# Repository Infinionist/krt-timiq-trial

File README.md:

# krt-timiq-trial

A placement trial of KiCadRoutingTools (KRT) v0.23.7 (commit db056e03) on the CERN TimIQ RF board.
@edgehero suggested the board. The work was done by a designer (Infinionist) driving Claude Code.
The board has 465 parts, 8 layers, 6 shield cans (J7-J12) and sits in a Hammond 1590Q lid.

This is raw working material, not a polished report. Point your own model at it.
Start with `notes/timiq.md`, then `runs/v6/REPORT.md`.

v6 is the run done the skill's way: the model reads the schematic, gets the physical facts and the
designer's intent, and runs the skill's rounds (3, 3 and 12 seeds). The earlier runs were our own
scripted variants and show where our setup went wrong.

Board source (CERN open hardware): https://gitlab.com/ohwr/project/timiq/timiq-hw

## Folders

- `notes/`: feedback notes for KRT (`timiq.md`: gaps, workarounds, where we leaned on the human board,
  results) and plans (`PLAN.md`, `PLAN-v2.md`).
- `scripts/`: small helper scripts shared by several runs.
- `runs/run1/`: first attempt, KRT's skill driven by Claude Opus with an empty design brief. 12 seeds, judge,
  final board with 557 blocking nets after routing.
- `runs/run2/`: second attempt. Plan v2 (see `notes/PLAN-v2.md`), prompt, inputs, and the can/hole/membership work files.
- `runs/v2/`: placer-only variant with our KRT patch. Scripts, intent, seeds, renders, human-board render.
- `runs/v3/`: loose anchor zones per can, courtyards synthesized, flippable faces. All 12 seeds illegal
  (our input bugs: a fixed LED in a hole keep-out, DAC bigger than its zone, overlapping zones). KRT flagged
  them only after 4 h of placing.
- `runs/v4/`: tight power strip and cans placed inside fixed zones, 6 seeds of 42 min. All 6 illegal
  (15-25 parts with no legal pose, mostly power). Our tiles were too tight.
- `runs/v5/`: holds `seeds-run1` (v5-1: all 282 can members inside their can, not DONE: 76 proximity misses,
  power entry split from regulators), `seeds-v4`, `seeds-run2` and `seeds` (v5b: power as loose groups, ICs locked
  on F; 3 seeds, all illegal, 7-9 parts with no legal pose). `cmp/` has the human-board comparison renders
  (human vs seed vs routed seed). `movie/` has the 3D placement movie.
- `runs/v6/`: the skill as written. `REPORT.md`, `final.kicad_pcb` (+ `.kicad_pro`, `final_intent.json`),
  `groups.json`, rounds `r1`/`r2`/`r3` (seed reports, logs, judge files, renders, best board per round),
  `best_*` renders, quick-route renders, `movie_r1..r3/placed_3d.mp4`, `ledger.jsonl`, start board, build scripts.
  Round 3: 6 of 12 seeds legal with 0 floorplan errors, the first legal placement of this board. Kept seed 7:
  buildable with BOX1 waivers, quick route 88 blocking (39 unrouted, 49 broken). Not DONE by the skill's table.
- `runs/retest/`: the #1457 retest (2026-10-30) at KRT main 8f0c7ef4 (v0.23.7), with the cans kept on the board as
  `cans[]` rows. `REPORT.md` (the run's own report), `compare.json` (vs v6), `final.kicad_pcb`, `intent.json`, `TimIQ_RF.design-brief.json` (the six `cans[]` rows),
  `seed3_with_cans.mp4` (the kept seed, with the can walls drawn in by `repro/add_cans.py`), `placed_3d.mp4`
  (make_movie as run), `repro/` (wall check, board_score repro). 12 of 12 seeds legal; kept seed 3.

## What was trimmed

- No vendor datasheets (copyright) and no KRT clone. Get KRT v0.23.7 from its own repo.
- Route working dirs (`s*_route/`) were dropped except `runs/v6/r3/s7_route`.
- Only the best few seed boards of each round or run are kept. The seed `.json` reports and logs are all there.
- `*.kicad_prl` files and movie frame directories (`placed_movie3d/`) were dropped; the `.mp4` files are kept.
- `runs/v6/preflight_r1.txt` was over 5 MB in the original; it keeps its first and last 300 lines only.
- The name of the designer was replaced with `Infinionist` and home paths with `~`.

## Honest limits

The runs say as much about our setup as about KRT. The cans were taken off the board as a workaround (KRT has no
way to place parts inside a fixed can). J7-J10 poses, can membership and hole clearances follow the human board.
See "Where we cheated or leaned on the human board" in `notes/timiq.md`.

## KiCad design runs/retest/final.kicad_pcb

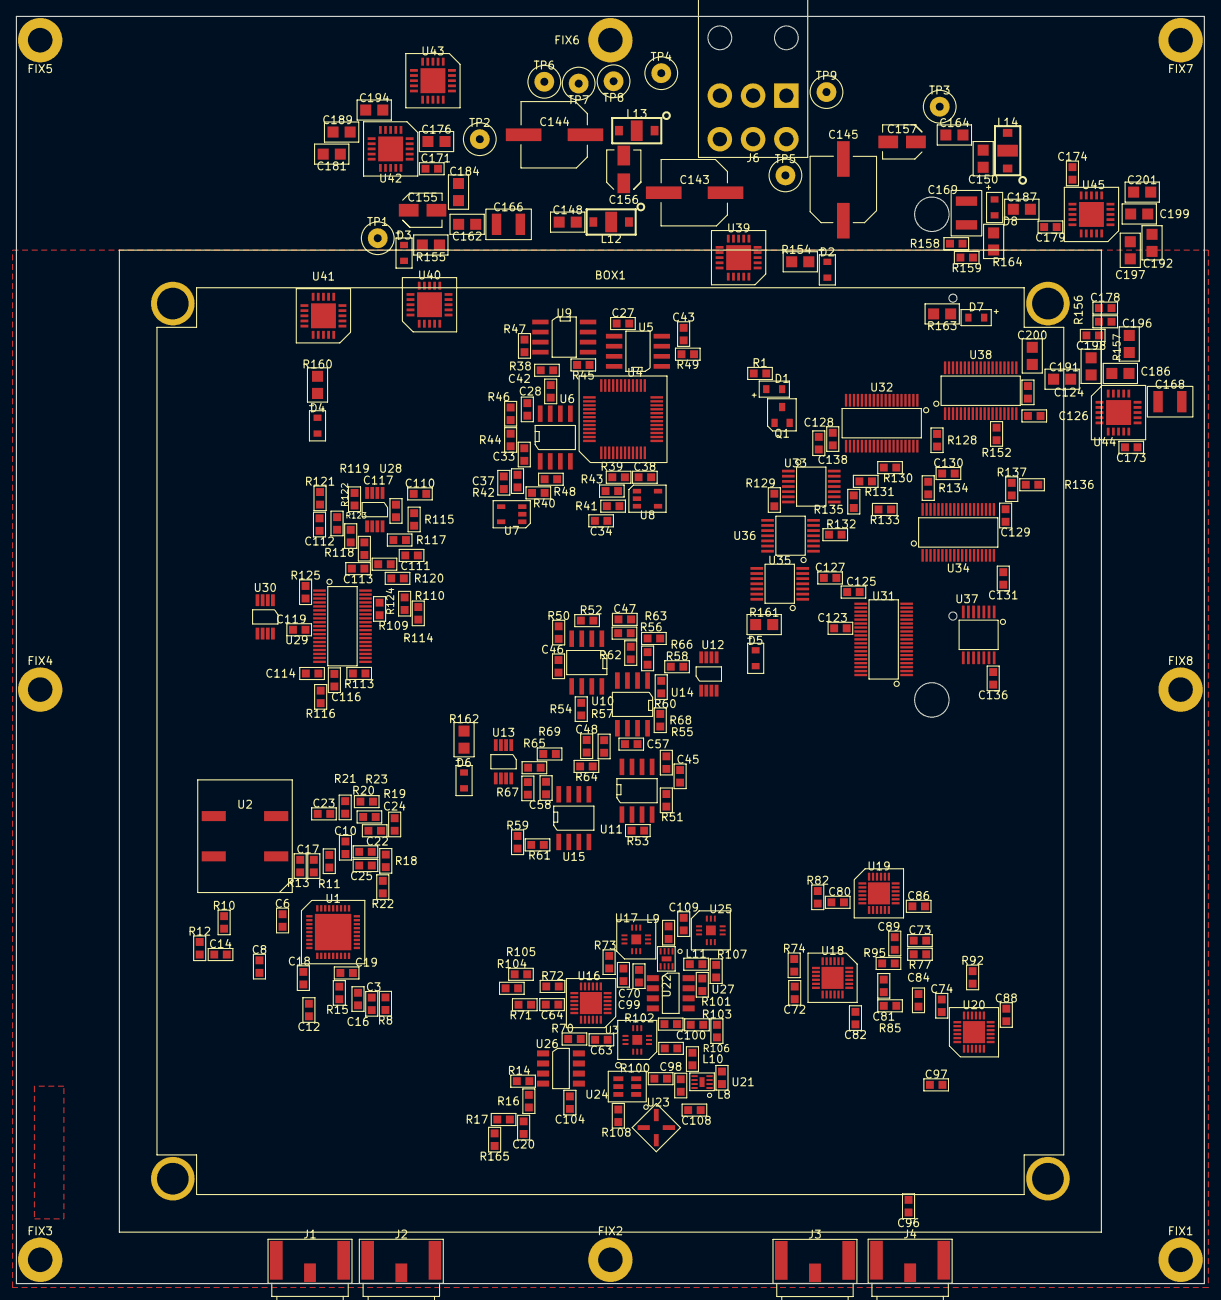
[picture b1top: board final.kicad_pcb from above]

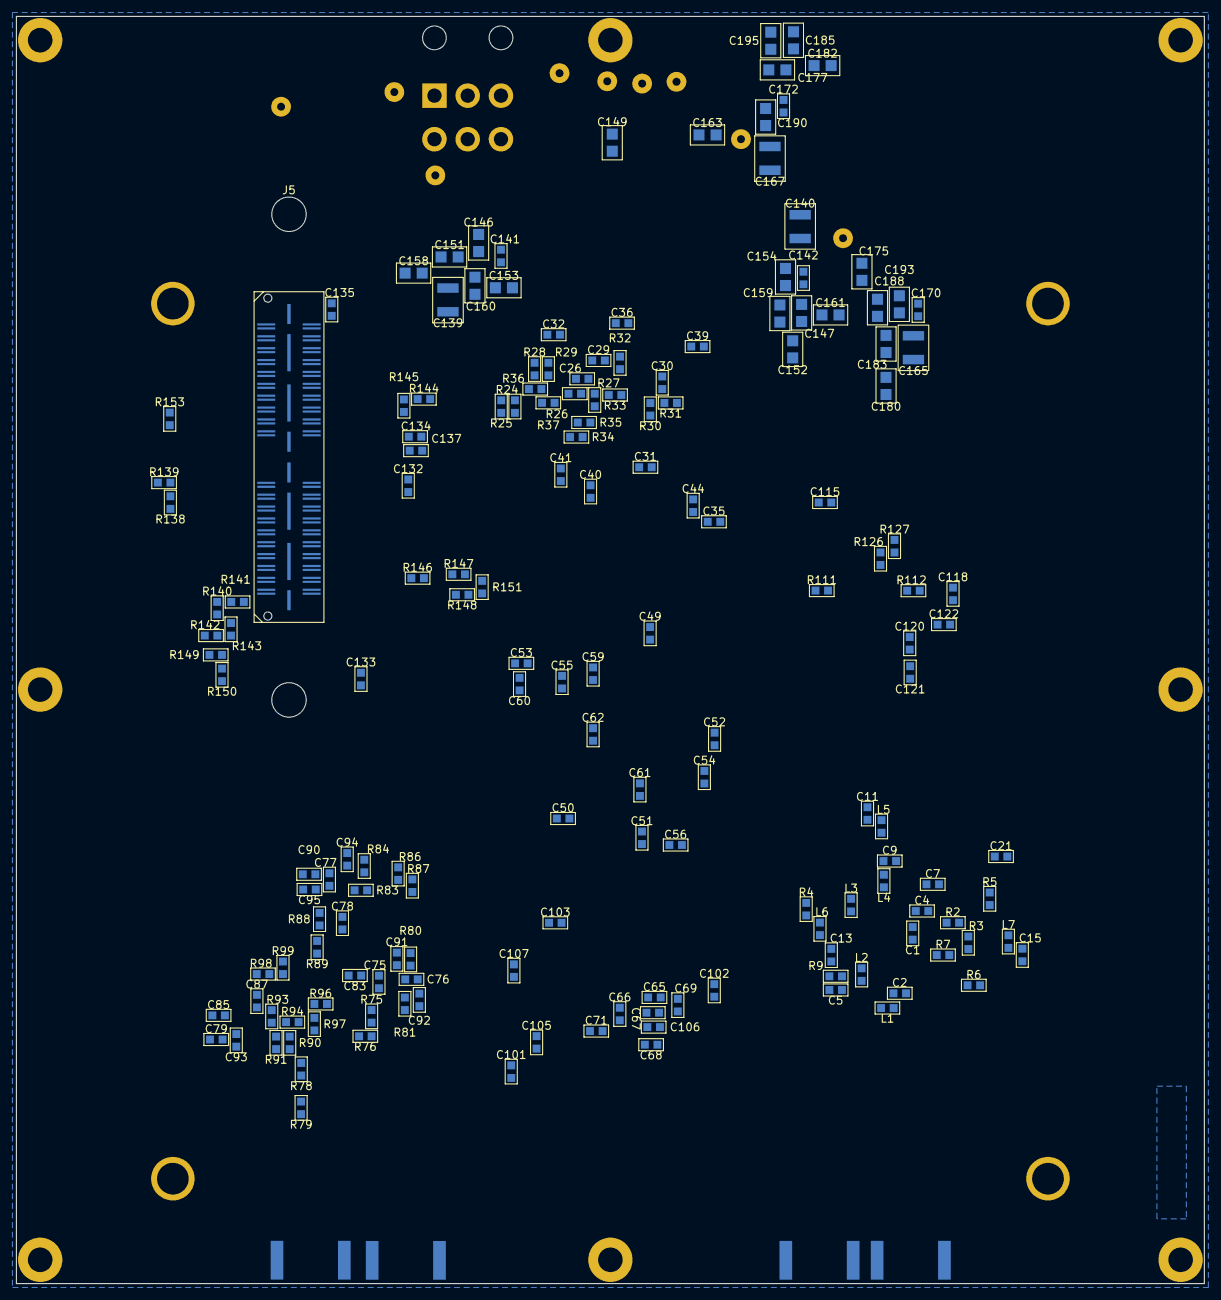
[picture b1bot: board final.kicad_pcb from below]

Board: 8 copper layers, 150.0 x 160.0 mm, 458 parts (167 on the bottom side), 298 nets, no tracks yet.

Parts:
BOX1: 1590Q; SOLEIL-1590Q
C1, C4, C6, C8, C65, C66, C74, C75, C82, C83, C90, C91: 10pF-50V-5p-Ceramic-0603; SOLEIL-0603
C2, C3, C7, C9, C11, C12, C13, C15, C24, C51, C52, C55, C56, C57, C58, C119: 100nF-50V-10p-Ceramic-0603; SOLEIL-0603
C5, C10, C33, C34, C37, C38, C120, C141, C142, C170, C171, C172, C173, C174: 1uF-25V-10p-Ceramic-0603; SOLEIL-0603
C14, C69, C71, C78, C79, C86, C87, C94, C95, C100, C102, C104, C106: 4.7uF-6.3V-10p-Ceramic-0603; SOLEIL-0603
C16, C20, C23, C27, C28, C42, C43, C47, C48, C63, C64, C70, C72, C73, C80, C81, C88, C89, C96, C97, C98, C99, C101, C103, C105, C107, C108, C109: 100pF-50V-5p-Ceramic-0603; SOLEIL-0603
C17, C19, C22, C25: 22nF-50V-10p-Ceramic-0603; SOLEIL-0603
C18: 2.2nF-50V-5p-Ceramic-0603; SOLEIL-0603
C21, C67, C68, C76, C77, C84, C85, C92, C93: 1nF-50V-5p-Ceramic-0603; SOLEIL-0603
C26, C29, C30, C31, C32, C35, C36, C39, C40, C41, C44, C45, C46, C49, C50, C59, C60, C61, C62, C114, C115, C116, C117, C118, C123, C124, C125, C126, C127, C128, C129, C130, C131, C132, C133, C134, C135, C136, C137, C138, C178, C179: 10nF-25V-5p-Ceramic-0603; SOLEIL-0603
C53, C54, C122: 10uF-6.3V-10p-Ceramic-0603; SOLEIL-0603
C110, C111: 330pF-50V-5p-Ceramic-0603; SOLEIL-0603
C112, C113: 1.5nF-50V-5p-Ceramic-0603; SOLEIL-0603
C121: 22uF-10V-20p-Ceramic-0603; SOLEIL-0603
C139, C140, C165, C166, C167, C168, C169: 10uF-25V-10p-Ceramic-1210; SOLEIL-1210
C143, C144, C145: 100uF-16V-20p-Al-TypeE; SOLEIL-TYPEE
C146, C147, C151, C152, C153, C154, C158, C159, C160, C161, C175, C176, C177, C180, C181, C182, C183, C184, C185, C186, C187, C188, C189, C190, C191, C192, C193, C194, C195, C196, C197, C198, C199, C200, C201: 10uF-16V-10p-Ceramic-0805; SOLEIL-0805
C148, C149, C150, C162, C163, C164: 100nF-50V-10p-Ceramic-0805; SOLEIL-0805
C155, C156, C157: 10uF-16V-20p-Al-TypeB; SOLEIL-TYPEB
D1, D2, D3, D4, D5, D6, D7, D8: LG_M67K-G1J2-24; SOLEIL-M67K
FIX1, FIX2, FIX3, FIX4, FIX5, FIX6, FIX7, FIX8: D_3mm1; SOLEIL-D_3mm1
J1, J2, J3, J4: 132430; SOLEIL-SMA-132430
J5: QSH-040-01-F-D-DP-A; SOLEIL-QSH-040-01-F-D-DP-A
J6: 39-30-1061; SOLEIL-39-30-1061
L1, L2, L3, L4, L5, L6, L7: BLM18AG102SN1D; SOLEIL-0603
L8, L9: 10nH-1.4A-2p-4.3GHz-0603; SOLEIL-0603
L10, L11: 8.2nH-700mA-2p-4.2GHz-0603; SOLEIL-0603
L12, L13, L14: NFM41PC155B1H3L; SOLEIL-NFM41P
Q1: BSH103; SOLEIL-SOT23-3
R1, R2, R5, R7, R38, R39, R44, R45, R48, R49, R50, R51, R52, R53, R110, R112, R114, R125, R127, R129, R130, R131: 1K-0.166W-0.1P-0603; SOLEIL-0603
R3, R13, R22, R25, R27, R29, R31, R33, R35, R37, R72, R76, R79, R81, R84, R87, R89, R91, R94, R97, R99, R133, R135, R137, R139, R141, R143, R145, R146, R147, R148, R150, R152, R153: 4K7-0.100W-0.1P-0603; SOLEIL-0603
R4, R6, R24, R26, R28, R30, R32, R34, R36, R40, R41, R42, R43, R75, R78, R80, R83, R86, R88, R90, R93, R96, R98, R109, R111, R113, R128, R132, R134, R136, R138, R140, R142, R144, R149, R151: 10k-0.125W-1P-0603; SOLEIL-0603
R8, R10, R70, R71, R73, R74, R77, R82, R85, R92, R95, R100, R101, R108, R165: 50R5-0.150W-0.1P-0603; SOLEIL-0603
R9, R12: 4R7-0.100W-1P-0603; SOLEIL-0603
R11, R46, R47: 10R-0.125W-1P-0603; SOLEIL-0603
R14, R17, R19, R23: 330R-0.250W-1P-0603; SOLEIL-0603
R15, R54, R55, R106, R107: 0R-0.100W-1P-0603; SOLEIL-0603
R16, R20, R21: 18R-0.250W-1P-0603; SOLEIL-0603
R18: 820R-0.250W-1P-0603; SOLEIL-0603
R56, R57: 4K02-0.166W-0.1P-0603; SOLEIL-0603
R58, R59, R62, R64: 976R-0.166W-0.1P-0603; SOLEIL-0603
R60, R61: 576R-0.166W-0.1P-0603; SOLEIL-0603
R63, R65: 62R-0.200W-1P-0603; SOLEIL-0603
R66, R67: 1K5-0.166W-0.1P-0603; SOLEIL-0603
R68, R69: 1K2-0.100W-0.1P-0603; SOLEIL-0603
R102, R104: 5K11-0.166W-0.1P-0603; SOLEIL-0603
R103, R105: 49R9-0.166W-0.1P-0603; SOLEIL-0603
R115, R116: 7K5-0.166W-0.1P-0603; SOLEIL-0603
R117, R118: 14K-0.166W-0.1P-0603; SOLEIL-0603
R119, R120, R126: 10K-0.166W-0.1P-0603; SOLEIL-0603
R121, R122: 10M-0.100W-1P-0603; SOLEIL-0603
R123, R124: 88K7-0.166W-0.1P-0603; SOLEIL-0603
R154, R155, R163: 1K5-0.125W-1P-0805; SOLEIL-0805
R156: 332K-0.100W-1P-0603; SOLEIL-0603
R157: 102K-0.100W-1P-0603; SOLEIL-0603
R158: 1M24-0.100W-1P-0603; SOLEIL-0603
R159: 105K-0.100W-1P-0603; SOLEIL-0603
R160, R161: 1K-0.125W-1P-0805; SOLEIL-0805
R162, R164: 4K7-0.125W-1P-0805; SOLEIL-0805
TP1, TP2, TP3, TP4, TP5, TP6, TP7, TP8, TP9: TEST-22; SOLEIL-TEST-22
U1: LMX2541SQ2690E; SOLEIL-WQFN36
U2: CVHD-950M-108.3681; SOLEIL-SMD9x14
U3, U17, U25: GP2Y+; SOLEIL-DQ1225
U4: LTC2758ACLX; SOLEIL-LQFP48
U5, U6: LT1012ACS8; SOLEIL-SOIC8NB
U7, U8: LTC2054HVCS5; SOLEIL-SOT23-5
U9: LTC6241HVCS8; SOLEIL-SOIC8NB
U10, U11: LT1360CS8; SOLEIL-SOIC8NB
U12, U13: LTC6655BHMS8-1.25; SOLEIL-MSOP8
U14, U15: LT6600CS8-2.5; SOLEIL-SOIC8NB
U16: HMC1097LP4E; SOLEIL-WQFN24
U18, U19, U20: HMC705LP4E; SOLEIL-WQFN24
U21, U22: PMA2-43LN+; SOLEIL-MC1631
U23: GAT-5+; SOLEIL-FG873
U24: QCN-34+; SOLEIL-FV1206-1
U26, U27: SIM-73L+; SOLEIL-HV1195
U28: OPA2209AIDGKR; SOLEIL-MSOP8
U29: ADS8694IDBT; SOLEIL-TSSOP38-0.5
U30: LTC6655BHMS8-4.096; SOLEIL-MSOP8
U31, U32, U34: SN75LVDT388ADBT; SOLEIL-TSSOP38-0.5
U33, U35, U36, U37: SN74LV4T125PWR; SOLEIL-TSSOP14-0.65
U38: SN75LVDS389DBT; SOLEIL-TSSOP38-0.5
U39, U40, U41, U42, U43: TPS7A4700; SOLEIL-VQFN20
U44, U45: TPS7A3301; SOLEIL-VQFN20

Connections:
3V3_1: C1.1, C4.1, C6.1, C7.1, C8.1, C21.1, C175.1, C180.1, C183.1, C188.1, C193.1, L1.1, L2.1, L3.1, L4.1, L5.1, L6.1, L7.1, R4.1, R6.1, R160.1, U1.3, U1.7, U1.29, U1.31, U2.4, U41.1, U41.3, U41.20
3V3_2: C116.1, C123.1, C124.1, C125.1, C126.1, C127.1, C128.1, C129.1, C130.1, C131.1, C133.1, C134.1, C135.1, C137.1, C176.1, C181.1, C184.1, C189.1, C194.1, R109.1, R111.1, R113.1, R126.1, R128.1, R132.1, R134.1, R136.1, R138.1, R140.1, R142.1, R144.1, R149.1, R161.1, U29.34, U31.21, U31.29, U31.37, U32.21, U32.29, U32.37, U34.21, U34.29, U34.37, U35.14, U38.2, U38.10, U38.18, U42.1, U42.3, U42.20
5V_1: C74.1, C75.1, C76.1, C77.1, C78.1, C79.1, C82.1, C83.1, C84.1, C85.1, C86.1, C87.1, C90.1, C91.1, C92.1, C93.1, C94.1, C95.1, C136.1, C138.1, C146.1, C151.1, C153.1, C158.1, C160.1, R75.1, R78.1, R80.1, R83.1, R86.1, R88.1, R90.1, R93.1, R96.1, R98.1, R154.1, U18.9, U18.19, U19.9, U19.19, U20.9, U20.19, U36.14, U37.14, U39.1, U39.3, U39.20
5V_2: C26.1, C35.1, C36.1, C41.1, C51.1, C52.1, C59.1, C60.1, C65.1, C66.1, C67.1, C68.1, C69.1, C71.1, C104.1, C106.1, C114.1, C117.1, C118.1, C119.1, C132.1, C147.1, C152.1, C154.1, C159.1, C161.1, R1.1, R24.1, R26.1, R28.1, R30.1, R32.1, R34.1, R36.1, R102.1, R104.1, R106.1, R107.1, R151.1, R155.1, U4.5, U4.6, U4.16, U4.31, U4.32, U4.37, U4.38, U4.47, U4.48, U7.5, U8.5, U9.8, U12.1, U12.2, U13.1, U13.2, U14.3, U15.3, U16.18, U16.24, U28.8, U29.9, U29.30, U30.1, U30.2, U33.14, U40.1, U40.3, U40.20
7V5: C139.1, C140.1, C155.1, C162.1, C165.1, C166.1, L12.3, TP1.1, U39.13, U39.15, U39.16, U40.13, U40.15, U40.16, U41.13, U41.15, U41.16, U42.13, U42.15, U42.16
15V: C29.1, C30.1, C45.1, C46.1, C177.1, C182.1, C185.1, C190.1, C195.1, R162.1, U5.7, U6.7, U10.7, U11.7, U43.1, U43.3, U43.20
24V: C156.1, C163.1, C167.1, L13.3, TP2.1, U43.13, U43.15, U43.16
-5V: C39.1, C40.1, C44.1, C61.1, C62.1, C115.1, C178.1, C186.1, C191.1, C196.1, C198.1, C200.1, R156.1, R163.1, U7.2, U8.2, U9.4, U14.6, U15.6, U28.4, U44.1, U44.20
-15V: C31.1, C32.1, C49.1, C50.1, C179.1, C187.1, C192.1, C197.1, C199.1, C201.1, R158.1, R164.1, U5.4, U6.4, U10.4, U11.4, U45.1, U45.20
-24V: C157.2, C164.1, C168.1, C169.1, L14.3, TP3.1, U44.13, U44.15, U44.16, U45.13, U45.15, U45.16
/TOP/ADC//ADC_CS: R109.2, U29.38, U32.26
/TOP/ADC//ADC_RST: R111.2, U29.2, U32.27
/TOP/ADC/ADC_ALARM: R114.1, U29.35, U38.8
/TOP/ADC/ADC_MISO: R113.2, U29.36, U38.7
/TOP/ADC/ADC_MOSI: R112.1, U29.1, U32.23
/TOP/ADC/ADC_SCK: R110.1, U29.37, U32.24
/TOP/ADC/MIXERout0: R115.1, U26.2
/TOP/ADC/MIXERout1: R116.1, U27.2
/TOP/DAC Interface/DAC_I: C47.2, R54.2, R56.2, R62.1, U4.39, U4.40, U10.6
/TOP/DAC Interface/DAC_Q: C48.2, R55.2, R57.2, R64.1, U4.45, U4.46, U11.6
/TOP/DAC Interface/I_N: U14.5, U16.22
/TOP/DAC Interface/I_P: U14.4, U16.21
/TOP/DAC Interface/Q_N: U15.5, U16.9
/TOP/DAC Interface/Q_P: U15.4, U16.10
/TOP/DAC//DAC_CS: U4.11, U33.3
/TOP/DAC/DAC_MISO: R151.2, U4.14, U35.2
/TOP/DAC/DAC_MOSI: U4.12, U33.8
/TOP/DAC/DAC_SCK: U4.13, U33.6
/TOP/Frequency dividers/FD0_BYP: U18.24, U36.3
/TOP/Frequency dividers/FD0_DIV1: R80.2, R81.1, U18.7
/TOP/Frequency dividers/FD0_N0: U18.21, U36.8
/TOP/Frequency dividers/FD0_N1: U18.22, U36.6
/TOP/Frequency dividers/FD0_N2: R75.2, R76.1, U18.23
/TOP/Frequency dividers/FD0_S0: R78.2, R79.1, U18.20
/TOP/Frequency dividers/FD1_BYP: U19.24, U36.11
/TOP/Frequency dividers/FD1_DIV1: R88.2, R89.1, U19.7
/TOP/Frequency dividers/FD1_N0: U19.21, U37.6
/TOP/Frequency dividers/FD1_N1: U19.22, U37.3
/TOP/Frequency dividers/FD1_N2: R83.2, R84.1, U19.23
/TOP/Frequency dividers/FD1_S0: R86.2, R87.1, U19.20
/TOP/Frequency dividers/FD2_BYP: U20.24, U37.8
/TOP/Frequency dividers/FD2_DIV1: U20.7, U37.11
/TOP/Frequency dividers/FD2_N0: R96.2, R97.1, U20.21
/TOP/Frequency dividers/FD2_N1: R93.2, R94.1, U20.22
/TOP/Frequency dividers/FD2_N2: R90.2, R91.1, U20.23
/TOP/Frequency dividers/FD2_S0: R98.2, R99.1, U20.20
/TOP/Frequency dividers/IQout1: C72.1, R74.1, U17.9
/TOP/Frequency mixers/IQout0: C99.1, R101.1, U17.7
/TOP/Frequency mixers/PLLout0: C98.1, R100.1, U3.7
/TOP/IQ modulator/PLLout1: C63.1, R70.1, U3.9
/TOP/PLL/PLL_CE: R4.2, U1.11, U31.35
/TOP/PLL/PLL_CLK: R5.1, U1.33, U31.31
/TOP/PLL/PLL_DATA: R7.1, U1.32, U31.32
/TOP/PLL/PLL_ENout: R6.2, U1.24, U31.34
/TOP/PLL/PLL_IN: C3.1, U1.21
/TOP/PLL/PLL_LE: R2.1, U1.34, U31.27
/TOP/PLL/PLL_LOCKED: Q1.1, R3.1, U1.20, U38.5
/TOP/PLL/PLL_OUT: C16.1, U1.36
/TOP/digital interface//ADC_CS-N: J5.63, U32.14
/TOP/digital interface//ADC_CS-P: J5.61, U32.13
/TOP/digital interface//ADC_RST-N: J5.59, U32.12
/TOP/digital interface//ADC_RST-P: J5.57, U32.11
/TOP/digital interface//DAC_CS-N: J5.43, U32.2
/TOP/digital interface//DAC_CS-P: J5.41, U32.1
/TOP/digital interface/ADC_ALARM-N: J5.56, U38.31
/TOP/digital interface/ADC_ALARM-P: J5.54, U38.32
/TOP/digital interface/ADC_MISO-N: J5.52, U38.33
/TOP/digital interface/ADC_MISO-P: J5.50, U38.34
/TOP/digital interface/ADC_MOSI-N: J5.71, U32.19
/TOP/digital interface/ADC_MOSI-P: J5.69, U32.18
/TOP/digital interface/ADC_SCK-N: J5.67, U32.17
/TOP/digital interface/ADC_SCK-P: J5.65, U32.16
/TOP/digital interface/DAC_ENA: J5.73, U32.36
/TOP/digital interface/DAC_ENB: J5.75, U32.33
/TOP/digital interface/DAC_ENC: J5.77, U32.25
/TOP/digital interface/DAC_END: J5.79, U32.22
/TOP/digital interface/DAC_MISO-N: J5.48, U38.35
/TOP/digital interface/DAC_MISO-P: J5.46, U38.36
/TOP/digital interface/DAC_MOSI-N: J5.51, U32.7
/TOP/digital interface/DAC_MOSI-P: J5.49, U32.6
/TOP/digital interface/DAC_SCK-N: J5.47, U32.4
/TOP/digital interface/DAC_SCK-P: J5.45, U32.3
/TOP/digital interface/D_ENA: J5.58, U38.4
/TOP/digital interface/D_ENB: J5.60, U38.16
/TOP/digital interface/FD0_BYP-N: J5.4, U34.2
/TOP/digital interface/FD0_BYP-P: J5.2, U34.1
/TOP/digital interface/FD0_N0-N: J5.12, U34.7
/TOP/digital interface/FD0_N0-P: J5.10, U34.6
/TOP/digital interface/FD0_N1-N: J5.8, U34.4
/TOP/digital interface/FD0_N1-P: J5.6, U34.3
/TOP/digital interface/FD1_BYP-N: J5.16, U34.9
/TOP/digital interface/FD1_BYP-P: J5.14, U34.8
/TOP/digital interface/FD1_N0-N: J5.24, U34.14
/TOP/digital interface/FD1_N0-P: J5.22, U34.13
/TOP/digital interface/FD1_N1-N: J5.20, U34.12
/TOP/digital interface/FD1_N1-P: J5.18, U34.11
/TOP/digital interface/FD2_BYP-N: J5.28, U34.17
/TOP/digital interface/FD2_BYP-P: J5.26, U34.16
/TOP/digital interface/FD2_DIV1-N: J5.32, U34.19
/TOP/digital interface/FD2_DIV1-P: J5.30, U34.18
/TOP/digital interface/FD_ENA: J5.34, U34.36
/TOP/digital interface/FD_ENB: J5.36, U34.33
/TOP/digital interface/FD_ENC: J5.38, U34.25
/TOP/digital interface/FD_END: J5.40, U34.22
/TOP/digital interface/PLL_CE-N: J5.3, U31.2
/TOP/digital interface/PLL_CE-P: J5.1, U31.1
/TOP/digital interface/PLL_CLK-N: J5.15, U31.9
/TOP/digital interface/PLL_CLK-P: J5.13, U31.8
/TOP/digital interface/PLL_DATA-N: J5.11, U31.7
/TOP/digital interface/PLL_DATA-P: J5.9, U31.6
/TOP/digital interface/PLL_ENA: J5.33, U31.36
/TOP/digital interface/PLL_ENB: J5.35, U31.33
/TOP/digital interface/PLL_ENC: J5.37, U31.25
/TOP/digital interface/PLL_END: J5.39, U31.22
/TOP/digital interface/PLL_ENout-N: J5.7, U31.4
/TOP/digital interface/PLL_ENout-P: J5.5, U31.3
/TOP/digital interface/PLL_LE-N: J5.19, U31.12
/TOP/digital interface/PLL_LE-P: J5.17, U31.11
/TOP/digital interface/PLL_LOCKED-N: J5.44, U38.37
/TOP/digital interface/PLL_LOCKED-P: J5.42, U38.38
/TOP/digital interface/SPARE0-N: J5.23, U31.14
/TOP/digital interface/SPARE0-P: J5.21, U31.13
/TOP/digital interface/SPARE1-N: J5.27, U31.17
/TOP/digital interface/SPARE1-P: J5.25, U31.16
/TOP/digital interface/SPARE2-N: J5.31, U31.19
/TOP/digital interface/SPARE2-P: J5.29, U31.18
/TOP/digital interface/SPARE3-N: J5.55, U32.9
/TOP/digital interface/SPARE3-P: J5.53, U32.8
/TOP/digital interface/SPARE4-N: J5.64, U38.26
/TOP/digital interface/SPARE4-P: J5.62, U38.27
/TOP/digital interface/SPARE5-N: J5.68, U38.24
/TOP/digital interface/SPARE5-P: J5.66, U38.25
/TOP/digital interface/SPARE6-N: J5.72, U38.22
/TOP/digital interface/SPARE6-P: J5.70, U38.23
/TOP/digital interface/SPARE7-N: J5.76, U38.20
/TOP/digital interface/SPARE7-P: J5.74, U38.21
GND: BOX1.1, BOX1.3, BOX1.5, BOX1.7, C1.2, C2.2, C4.2, C5.2, C6.2, C8.2, C9.2, C10.2, C11.2, C12.2, C13.2, C14.2, C15.2, C17.2, C18.2, C19.2, C21.2, C26.2, C29.2, C30.2, C31.2, C32.2, C33.2, C34.2, C35.2, C36.2, C39.2, C40.2, C41.2, C44.2, C45.2, C46.2, C49.2, C50.2, C51.2, C52.2, C53.2, C54.2, C55.2, C56.2, C57.2, C58.2, C59.2, C60.2, C61.2, C62.2, C65.2, C66.2, C67.2, C68.2, C69.2, C71.2, C74.2, C75.2, C76.2, C77.2, C78.2, C79.2, C82.2, C83.2, C84.2, C85.2, C86.2, C87.2, C90.2, C91.2, C92.2, C93.2, C94.2, C95.2, C100.2, C101.2, C102.2, C103.2, C104.2, C105.2, C106.2, C107.2, C112.2, C113.2, C114.2, C115.2, C116.2, C117.2, C118.2, C119.2, C120.2, C121.2, C122.2, C123.2, C124.2, C125.2, C126.2, C127.2, C128.2, C129.2, C130.2, C131.2, C132.2, C133.2, C134.2, C135.2, C136.2, C137.2, C138.2, C139.2, C140.2, C141.2, C142.2, C143.2, C144.2, C145.1, C146.2, C147.2, C148.2, C149.2, C150.2, C151.2, C152.2, C153.2, C154.2, C155.2, C156.2, C157.1, C158.2, C159.2, C160.2, C161.2, C162.2, C163.2, C164.2, C165.2, C166.2, C167.2, C168.2, C169.2, C170.2, C171.2, C172.2, C173.2, C174.2, C175.2, C176.2, C177.2, C180.2, C181.2, C182.2, C183.2, C184.2, C185.2, C186.2, C187.2, C188.2, C189.2, C190.2, C191.2, C192.2, C193.2, C194.2, C195.2, C196.2, C197.2, C198.2, C199.2, C200.2, C201.2, D2.2, D3.2, D4.2, D5.2, D6.2, D7.1, D8.1, FIX1.1, FIX2.1, FIX3.1, FIX4.1, FIX5.1, FIX6.1, FIX7.1, FIX8.1, J1.2, J1.3, J1.4, J1.5, J2.2, J2.3, J2.4, J2.5, J3.2, J3.3, J3.4, J3.5, J4.2, J4.3, J4.4, J4.5, J5.81, J5.82, J5.83, J5.84, J5.85, J5.86, J5.87, J5.88, J6.2, J6.4, J6.6, L12.2, L13.2, L14.2, Q1.2, R2.2, R3.2, R5.2, R7.2, R8.2, R10.2, R14.2, R17.2, R18.2, R19.2, R23.2, R25.2, R27.2, R29.2, R31.2, R33.2, R35.2, R37.2, R46.2, R47.2, R50.2, R51.2, R52.2, R53.2, R60.2, R61.2, R63.2, R65.2, R68.2, R69.2, R70.2, R71.2, R72.2, R73.2, R74.2, R76.2, R77.2, R79.2, R81.2, R82.2, R84.2, R85.2, R87.2, R89.2, R91.2, R92.2, R94.2, R95.2, R97.2, R99.2, R100.2, R101.2, R108.2, R110.2, R112.2, R114.2, R119.2, R120.2, R121.2, R122.2, R125.2, R127.2, R129.2, R130.2, R131.2, R133.2, R135.2, R137.2, R139.2, R141.2, R143.2, R145.2, R146.1, R147.1, R148.1, R150.2, R152.1, R153.1, R157.2, R159.2, R165.2, TP4.1, TP5.1, TP6.1, TP7.1, TP8.1, TP9.1, U1.0, U1.1, U1.10, U1.27, U2.2, U3.0, U3.1, U3.3, U3.4, U3.5, U3.6, U3.8, U3.10, U3.11, U3.12, U4.4, U4.7, U4.8, U4.9, U4.10, U4.15, U4.17, U4.18, U4.27, U4.28, U4.29, U4.30, U4.33, U4.42, U4.43, U5.3, U6.3, U7.3, U8.3, U12.3, U12.4, U12.5, U12.8, U13.3, U13.4, U13.5, U13.8, U16.0, U16.2, U16.5, U16.8, U16.11, U16.12, U16.14, U16.17, U16.19, U16.20, U16.23, U17.0, U17.1, U17.3, U17.4, U17.5, U17.6, U17.8, U17.10, U17.11, U17.12, U18.0, U18.1, U18.2, U18.3, U18.4, U18.5, U18.6, U18.8, U18.10, U18.13, U18.14, U18.17, U18.18, U19.0, U19.1, U19.2, U19.3, U19.4, U19.5, U19.6, U19.8, U19.10, U19.13, U19.14, U19.17, U19.18, U20.0, U20.1, U20.2, U20.3, U20.4, U20.5, U20.6, U20.8, U20.10, U20.13, U20.14, U20.17, U20.18, U21.0, U21.3, U21.4, U21.5, U21.6, U21.8, U22.0, U22.3, U22.4, U22.5, U22.6, U22.8, U23.2, U23.4, U24.2, U24.5, U25.0, U25.1, U25.3, U25.4, U25.5, U25.6, U25.8, U25.10, U25.11, U25.12, U26.1, U26.3, U26.5, U26.6, U26.7, U27.1, U27.3, U27.5, U27.6, U27.7, U29.6, U29.8, U29.17, U29.19, U29.28, U29.29, U29.31, U29.32, U29.33, U30.3, U30.4, U30.5, U30.8, U31.5, U31.10, U31.15, U31.20, U31.28, U31.30, U31.38, U32.5, U32.10, U32.15, U32.20, U32.28, U32.30, U32.38, U33.1, U33.4, U33.7, U33.10, U33.13, U34.5, U34.10, U34.15, U34.20, U34.28, U34.30, U34.38, U35.1, U35.4, U35.7, U35.10, U35.13, U36.1, U36.4, U36.7, U36.10, U36.13, U37.1, U37.4, U37.7, U37.10, U37.13, U38.1, U38.3, U38.9, U38.11, U38.17, U38.19, U39.0, U39.6, U39.7, U39.10, U40.0, U40.6, U40.7, U40.10, U41.0, U41.7, U41.8, U41.11, U41.12, U42.0, U42.7, U42.8, U42.11, U42.12, U43.0, U43.4, U43.5, U43.7, U43.9, U44.0, U44.7, U45.0, U45.7
unnamed: C2.1, L1.2, U1.28
unnamed: C3.2, J1.1, R8.1
unnamed: C5.1, R9.1
unnamed: C7.2, U1.30
unnamed: C9.1, L4.2, U1.14
unnamed: C10.1, R11.2
unnamed: C11.1, L5.2, U1.18
unnamed: C12.1, U1.9
unnamed: C13.1, L6.2, U1.13
unnamed: C14.1, R12.2
unnamed: C15.1, L7.2, U1.19
unnamed: C16.2, R14.1, R16.1
unnamed: C17.1, R13.2, U2.1
unnamed: C18.1, R13.1, R15.2, U1.15
unnamed: C19.1, C22.1, C25.1, R15.1, U1.16
unnamed: C20.1, J2.1, R165.1
unnamed: C20.2, R16.2, R17.1, U3.2
unnamed: C22.2, C25.2, R18.1, R22.2
unnamed: C23.1, U2.3
unnamed: C23.2, R21.1
unnamed: C24.1, U1.12
unnamed: C24.2, R19.1, R20.1
unnamed: C27.1, U4.34, U5.2
unnamed: C27.2, U4.35, U4.36, U5.6
unnamed: C28.1, U4.3, U6.2
unnamed: C28.2, U4.1, U4.2, U6.6
unnamed: C33.1, R40.2, R42.1
unnamed: C34.1, R41.2, R43.1
unnamed: C37.1, R42.2, U7.4
unnamed: C37.2, R44.1, U7.1
unnamed: C38.1, R43.2, U8.4
unnamed: C38.2, R45.1, U8.1
unnamed: C42.1, R38.2, R40.1, R48.1, U9.2
unnamed: C42.2, R48.2, R50.1, R54.1, U9.1, U10.3
unnamed: C43.1, R39.2, R41.1, R49.1, U9.6
unnamed: C43.2, R49.2, R51.1, R55.1, U9.7, U11.3
unnamed: C47.1, R52.1, R56.1, U10.2
unnamed: C48.1, R53.1, R57.1, U11.2
unnamed: C53.1, R58.1, U12.6, U12.7
unnamed: C54.1, R59.1, U13.6, U13.7
unnamed: C55.1, R58.2, R60.1, U14.2
unnamed: C56.1, R59.2, R61.1, U15.2
unnamed: C57.1, U14.7
unnamed: C58.1, U15.7
unnamed: C63.2, U16.3
unnamed: C64.1, R71.1
unnamed: C64.2, U16.4
unnamed: C70.1, U16.16
unnamed: C70.2, R73.1, U17.2
unnamed: C72.2, U18.12
unnamed: C73.1, R77.1
unnamed: C73.2, U18.11
unnamed: C80.1, R82.1, U18.15
unnamed: C80.2, U19.12
unnamed: C81.1, R85.1, U18.16
unnamed: C81.2, U19.11
unnamed: C88.1, R92.1, U19.15
unnamed: C88.2, U20.12
unnamed: C89.1, R95.1, U19.16
unnamed: C89.2, U20.11
unnamed: C96.1, U20.15
unnamed: C96.2, J3.1
unnamed: C97.1, U20.16
unnamed: C97.2, J4.1
unnamed: C98.2, L8.2, U21.2
unnamed: C99.2, L9.2, U22.2
unnamed: C100.1, R102.2, R103.1
unnamed: C101.1, L8.1, R103.2, U21.1
unnamed: C102.1, R104.2, R105.1
unnamed: C103.1, L9.1, R105.2, U22.1
unnamed: C105.1, L10.1, R106.2
unnamed: C107.1, L11.1, R107.2
unnamed: C108.1, L10.2, U21.7
unnamed: C108.2, U23.1
unnamed: C109.1, L11.2, U22.7
unnamed: C109.2, U25.2
unnamed: C110.1, R123.2, U28.1, U29.16
unnamed: C110.2, R115.2, R117.1
unnamed: C111.1, R124.2, U28.7, U29.18
unnamed: C111.2, R116.2, R118.1
unnamed: C112.1, R117.2, R121.1, U28.3
unnamed: C113.1, R118.2, R122.1, U28.5
unnamed: C120.1, C121.1, U29.7
unnamed: C122.1, U29.5, U30.6, U30.7
unnamed: C141.1, U39.14
unnamed: C142.1, U40.14
unnamed: C143.1, C148.1, J6.1, L12.1
unnamed: C144.1, C149.1, J6.3, L13.1
unnamed: C145.2, C150.1, J6.5, L14.1
unnamed: C170.1, U41.14
unnamed: C171.1, U42.14
unnamed: C172.1, U43.14
unnamed: C173.1, U44.14
unnamed: C174.1, U45.14
unnamed: C178.2, R156.2, R157.1, U44.3
unnamed: C179.2, R158.2, R159.1, U45.3
unnamed: D1.1, R1.2
unnamed: D1.2, Q1.3
unnamed: D2.1, R154.2
unnamed: D3.1, R155.2
unnamed: D4.1, R160.2
unnamed: D5.1, R161.2
unnamed: D6.1, R162.2
unnamed: D7.2, R163.2
unnamed: D8.2, R164.2
unnamed: L2.2, U1.23
unnamed: L3.2, U1.25
unnamed: R9.2, U1.26
unnamed: R10.1, U1.22
unnamed: R11.1, U1.2
unnamed: R12.1, U1.8
unnamed: R20.2, R21.2, R23.1
unnamed: R22.1, U1.17
unnamed: R24.2, R25.1, U4.19
unnamed: R26.2, R27.1, U4.26
unnamed: R28.2, R29.1, U4.20
unnamed: R30.2, R31.1, U4.23
unnamed: R32.2, R33.1, U4.24
unnamed: R34.2, R35.1, U4.25
unnamed: R36.2, R37.1, U4.22
unnamed: R38.1, U4.41
unnamed: R39.1, U4.44
unnamed: R44.2, R46.1, U9.3
unnamed: R45.2, R47.1, U9.5
unnamed: R62.2, R63.1, R66.1
unnamed: R64.2, R65.1, R67.1
unnamed: R66.2, U14.1
unnamed: R67.2, U15.1
unnamed: R68.1, U14.8
unnamed: R69.1, U15.8
unnamed: R72.1, U16.7
unnamed: R108.1, U24.3
unnamed: R119.1, R123.1, U28.2
unnamed: R120.1, R124.1, U28.6
unnamed: R125.1, U29.3
unnamed: R126.2, R127.1, U29.4
unnamed: R128.2, U32.35, U33.2
unnamed: R129.1, U32.34, U33.5
unnamed: R130.1, U32.32, U33.9
unnamed: R131.1, U32.31, U33.12
unnamed: R132.2, R133.1, U34.35, U36.2
unnamed: R134.2, R135.1, U34.34, U36.5
unnamed: R136.2, R137.1, U34.32, U36.9
unnamed: R138.2, R139.1, U34.31, U36.12
unnamed: R140.2, R141.1, U34.27, U37.2
unnamed: R142.2, R143.1, U34.26, U37.5
unnamed: R144.2, R145.1, U34.24, U37.9
unnamed: R146.2, U35.5
unnamed: R147.2, U35.9
unnamed: R148.2, U35.12
unnamed: R149.2, R150.1, U34.23, U37.12
unnamed: R152.2, U38.14
unnamed: R153.2, U38.15
unnamed: U23.3, U24.1
unnamed: U24.4, U26.4
unnamed: U24.6, U27.4
unnamed: U25.7, U26.8
unnamed: U25.9, U27.8
unnamed: U35.3, U38.6
unnamed: U35.6, U38.12
unnamed: U35.8, U38.13

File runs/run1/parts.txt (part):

TOP/ADC                  B87   C116   F RCL_SMD:SOLEIL-0603                10nF-25V-5p-Ceramic-0603 body=[3.111, 1.524]
TOP/ADC                  B87   C117   F RCL_SMD:SOLEIL-0603                10nF-25V-5p-Ceramic-0603 body=[3.111, 1.524]
TOP/ADC                  B87   C118   B RCL_SMD:SOLEIL-0603                10nF-25V-5p-Ceramic-0603 body=[3.111, 1.524]
TOP/ADC                  B88   R115   F RCL_SMD:SOLEIL-0603                7K5-0.166W-0.1P-0603 body=[3.111, 1.524]
TOP/ADC                  B88   R117   F RCL_SMD:SOLEIL-0603                14K-0.166W-0.1P-0603 body=[3.111, 1.524]
TOP/ADC                  B89   R119   F RCL_SMD:SOLEIL-0603                10K-0.166W-0.1P-0603 body=[3.111, 1.524]
TOP/ADC                  B89   R121   F RCL_SMD:SOLEIL-0603                10M-0.100W-1P-0603 body=[3.111, 1.524]
TOP/ADC                  B89   U28    F MSOP:SOLEIL-MSOP8                  OPA2209AIDGKR body=[3.205, 5.711]
TOP/ADC                  B90   C120   B RCL_SMD:SOLEIL-0603                1uF-25V-10p-Ceramic-0603 body=[3.111, 1.524]
TOP/ADC                  B90   C121   B RCL_SMD:SOLEIL-0603                22uF-10V-20p-Ceramic-0603 body=[3.111, 1.524]
TOP/ADC                  B90   U29    F TSSOP:SOLEIL-TSSOP38-0.5           ADS8694IDBT body=[10.935, 7.4]
TOP/ADC                  B91   R125   F RCL_SMD:SOLEIL-0603                1K-0.166W-0.1P-0603 body=[3.111, 1.524]
TOP/ADC                  B91   R126   B RCL_SMD:SOLEIL-0603                10K-0.166W-0.1P-0603 body=[3.111, 1.524]
TOP/ADC                  B91   R127   B RCL_SMD:SOLEIL-0603                1K-0.166W-0.1P-0603 body=[3.111, 1.524]
TOP/ADC                  B92   R120   F RCL_SMD:SOLEIL-0603                10K-0.166W-0.1P-0603 body=[3.111, 1.524]
TOP/ADC                  B92   R122   F RCL_SMD:SOLEIL-0603                10M-0.100W-1P-0603 body=[3.111, 1.524]
TOP/ADC                  B93   C119   F RCL_SMD:SOLEIL-0603                100nF-50V-10p-Ceramic-0603 body=[3.111, 1.524]
TOP/ADC                  B93   C122   B RCL_SMD:SOLEIL-0603                10uF-6.3V-10p-Ceramic-0603 body=[3.111, 1.524]
TOP/ADC                  B93   U30    F MSOP:SOLEIL-MSOP8                  LTC6655BHMS8-4.096 body=[3.205, 5.711]
TOP/ADC                  B94   R109   F RCL_SMD:SOLEIL-0603                10k-0.125W-1P-0603 body=[3.111, 1.524]
TOP/ADC                  B94   R110   F RCL_SMD:SOLEIL-0603                1K-0.166W-0.1P-0603 body=[3.111, 1.524]
TOP/ADC                  B94   R111   B RCL_SMD:SOLEIL-0603                10k-0.125W-1P-0603 body=[3.111, 1.524]
TOP/ADC                  B94   R112   B RCL_SMD:SOLEIL-0603                1K-0.166W-0.1P-0603 body=[3.111, 1.524]
TOP/ADC                  B94   R113   F RCL_SMD:SOLEIL-0603                10k-0.125W-1P-0603 body=[3.111, 1.524]
TOP/ADC                  B94   R114   F RCL_SMD:SOLEIL-0603                1K-0.166W-0.1P-0603 body=[3.111, 1.524]
TOP/ADC                  B95   C114   F RCL_SMD:SOLEIL-0603                10nF-25V-5p-Ceramic-0603 body=[3.111, 1.524]
TOP/ADC                  B95   C115   B RCL_SMD:SOLEIL-0603                10nF-25V-5p-Ceramic-0603 body=[3.111, 1.524]
TOP/DAC                  -     C26    B RCL_SMD:SOLEIL-0603                10nF-25V-5p-Ceramic-0603 body=[3.111, 1.524]
TOP/DAC                  B10   C27    F RCL_SMD:SOLEIL-0603                100pF-50V-5p-Ceramic-0603 body=[3.111, 1.524]
TOP/DAC                  B10   U4     F QFP:SOLEIL-LQFP48                  LTC2758ACLX body=[11.1, 10.928]
TOP/DAC                  B10   U5     F SO:SOLEIL-SOIC8NB                  LT1012ACS8 body=[5.08, 8.101]
TOP/DAC                  B11   C42    F RCL_SMD:SOLEIL-0603                100pF-50V-5p-Ceramic-0603 body=[3.111, 1.524]
TOP/DAC                  B11   R44    F RCL_SMD:SOLEIL-0603                1K-0.166W-0.1P-0603 body=[3.111, 1.524]
TOP/DAC                  B11   R46    F RCL_SMD:SOLEIL-0603                10R-0.125W-1P-0603 body=[3.111, 1.524]
TOP/DAC                  B11   R48    F RCL_SMD:SOLEIL-0603                1K-0.166W-0.1P-0603 body=[3.111, 1.524]
TOP/DAC                  B11   U9     F SO:SOLEIL-SOIC8NB                  LTC6241HVCS8 body=[5.08, 8.101]
TOP/DAC                  B12   C47    F RCL_SMD:SOLEIL-0603                100pF-50V-5p-Ceramic-0603 body=[3.111, 1.524]
TOP/DAC                  B12   R50    F RCL_SMD:SOLEIL-0603                1K-0.166W-0.1P-0603 body=[3.111, 1.524]
TOP/DAC                  B12   R52    F RCL_SMD:SOLEIL-0603                1K-0.166W-0.1P-0603 body=[3.111, 1.524]
TOP/DAC                  B12   R54    F RCL_SMD:SOLEIL-0603                0R-0.100W-1P-0603 body=[3.111, 1.524]
TOP/DAC                  B12   R56    F RCL_SMD:SOLEIL-0603                4K02-0.166W-0.1P-0603 body=[3.111, 1.524]
TOP/DAC                  B12   U10    F SO:SOLEIL-SOIC8NB                  LT1360CS8 body=[5.08, 8.101]
TOP/DAC                  B13   C33    F RCL_SMD:SOLEIL-0603                1uF-25V-10p-Ceramic-0603 body=[3.111, 1.524]
TOP/DAC                  B13   R38    F RCL_SMD:SOLEIL-0603                1K-0.166W-0.1P-0603 body=[3.111, 1.524]
TOP/DAC                  B13   R40    F RCL_SMD:SOLEIL-0603                10k-0.125W-1P-0603 body=[3.111, 1.524]
TOP/DAC                  B13   R42    F RCL_SMD:SOLEIL-0603                10k-0.125W-1P-0603 body=[3.111, 1.524]
TOP/DAC                  B14   C37    F RCL_SMD:SOLEIL-0603                1uF-25V-10p-Ceramic-0603 body=[3.111, 1.524]
TOP/DAC                  B14   U7     F SOT23:SOLEIL-SOT23-5               LTC2054HVCS5 body=[3.429, 4.699]
TOP/DAC                  B15   R24    B RCL_SMD:SOLEIL-0603                10k-0.125W-1P-0603 body=[3.111, 1.524]
TOP/DAC                  B15   R25    B RCL_SMD:SOLEIL-0603                4K7-0.100W-0.1P-0603 body=[3.111, 1.524]
TOP/DAC                  B15   R26    B RCL_SMD:SOLEIL-0603                10k-0.125W-1P-0603 body=[3.111, 1.524]
TOP/DAC                  B15   R27    B RCL_SMD:SOLEIL-0603                4K7-0.100W-0.1P-0603 body=[3.111, 1.524]
TOP/DAC                  B15   R28    B RCL_SMD:SOLEIL-0603                10k-0.125W-1P-0603 body=[3.111, 1.524]
TOP/DAC                  B15   R29    B RCL_SMD:SOLEIL-0603                4K7-0.100W-0.1P-0603 body=[3.111, 1.524]
TOP/DAC                  B15   R30    B RCL_SMD:SOLEIL-0603                10k-0.125W-1P-0603 body=[3.111, 1.524]
TOP/DAC                  B15   R31    B RCL_SMD:SOLEIL-0603                4K7-0.100W-0.1P-0603 body=[3.111, 1.524]
TOP/DAC                  B15   R32    B RCL_SMD:SOLEIL-0603                10k-0.125W-1P-0603 body=[3.111, 1.524]
TOP/DAC                  B15   R33    B RCL_SMD:SOLEIL-0603                4K7-0.100W-0.1P-0603 body=[3.111, 1.524]
TOP/DAC                  B16   R34    B RCL_SMD:SOLEIL-0603                10k-0.125W-1P-0603 body=[3.111, 1.524]
TOP/DAC                  B16   R35    B RCL_SMD:SOLEIL-0603                4K7-0.100W-0.1P-0603 body=[3.111, 1.524]
TOP/DAC                  B16   R36    B RCL_SMD:SOLEIL-0603                10k-0.125W-1P-0603 body=[3.111, 1.524]
TOP/DAC                  B16   R37    B RCL_SMD:SOLEIL-0603                4K7-0.100W-0.1P-0603 body=[3.111, 1.524]
TOP/DAC                  B17   C43    F RCL_SMD:SOLEIL-0603                100pF-50V-5p-Ceramic-0603 body=[3.111, 1.524]
TOP/DAC                  B17   R49    F RCL_SMD:SOLEIL-0603                1K-0.166W-0.1P-0603 body=[3.111, 1.524]
TOP/DAC                  B18   C48    F RCL_SMD:SOLEIL-0603                100pF-50V-5p-Ceramic-0603 body=[3.111, 1.524]
TOP/DAC                  B18   R51    F RCL_SMD:SOLEIL-0603                1K-0.166W-0.1P-0603 body=[3.111, 1.524]
TOP/DAC                  B18   R53    F RCL_SMD:SOLEIL-0603                1K-0.166W-0.1P-0603 body=[3.111, 1.524]
TOP/DAC                  B18   R55    F RCL_SMD:SOLEIL-0603                0R-0.100W-1P-0603 body=[3.111, 1.524]
TOP/DAC                  B18   R57    F RCL_SMD:SOLEIL-0603                4K02-0.166W-0.1P-0603 body=[3.111, 1.524]
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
